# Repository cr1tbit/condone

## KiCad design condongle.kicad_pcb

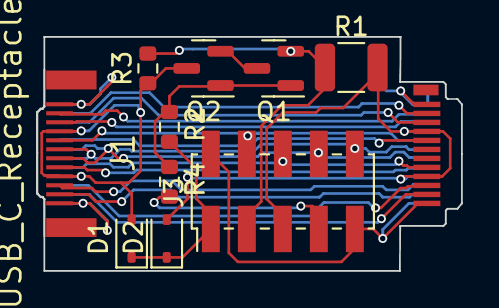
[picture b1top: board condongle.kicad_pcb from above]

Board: 2 copper layers, 23.6 x 13.0 mm, 11 parts (1 on the bottom side), 23 nets.

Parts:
D1, D2: 1N5819WS; D_SOD-323
J1: USB_C_Receptacle; 918-418K2022E40001
J3: Conn_02x05_Odd_Even; PinHeader_2x05_P2.00mm_Vertical_SMD
P1: USB_C_Plug; U261-24XN-4BS60
Q1, Q2: AO3401A; SOT-23
R1: 10mR; R_1210_3225Metric
R2, R4: 10k; R_0603_1608Metric
R3: 0R; R_0603_1608Metric

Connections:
/CC1: J1.A5 (CC1), J3.4, P1.A5 (CC)
/CC2: J1.B5 (CC2), J3.6, P1.B5 (VCONN)
/DM: J1.A7 (D-), J1.B7 (D-), J3.8, P1.A7 (D-)
/DP: J1.A6 (D+), J1.B6 (D+), J3.10, P1.A6 (D+)
/EXT_PWR: D1.1 (K), D2.1 (K), J3.1, R2.2
/LOADSW_CTRL: J3.7, R4.2
/VBUS_PLUG: D2.2 (A), J3.5, P1.A4 (VBUS), P1.A9 (VBUS), P1.B4 (VBUS), P1.B9 (VBUS), R1.2
/VBUS_R1: J3.3, Q1.2 (S), R1.1, R3.2
/VBUS_SOCK: D1.2 (A), J1.A4 (VBUS), J1.A9 (VBUS), J1.B4 (VBUS), J1.B9 (VBUS), Q2.3 (D), R3.1
GND: J1.A1 (GND), J1.A12 (GND), J1.B1 (GND), J1.B12 (GND), J3.2, J3.9, P1.A1 (GND), P1.A12 (GND), P1.B1 (GND), P1.B12 (GND)
unnamed: J1.B11 (RX1+), P1.B11 (RX1+)
unnamed: J1.B10 (RX1-), P1.B10 (RX1-)
unnamed: J1.A11 (RX2+), P1.A11 (RX2+)
unnamed: J1.A10 (RX2-), P1.A10 (RX2-)
unnamed: J1.A8 (SBU1), P1.A8 (SBU1)
unnamed: J1.B8 (SBU2), P1.B8 (SBU2)
unnamed: J1.S1 (SHIELD), P1.S1 (SHIELD)
unnamed: J1.A2 (TX1+), P1.A2 (TX1+)
unnamed: J1.A3 (TX1-), P1.A3 (TX1-)
unnamed: J1.B2 (TX2+), P1.B2 (TX2+)
unnamed: J1.B3 (TX2-), P1.B3 (TX2-)
unnamed: Q1.3 (D), Q2.2 (S)
unnamed: Q1.1 (G), Q2.1 (G), R2.1, R4.1

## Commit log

2023-06-11 add kicad files
